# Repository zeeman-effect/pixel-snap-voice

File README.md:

# pixel-snap-voice

A one-off slim rectangular **voice-note recorder** that snaps to the back of a **Google Pixel 10** using Pixelsnap / Qi2 magnets (MagSafe-style accessory rings work). It records raw WAV files, charges and dumps data over USB, can share those files over its own Wi-Fi network, and leaves transcription to a computer.

This repo holds hardware, firmware, simulation, and (later) a local transcription helper. The first board is meant to be ordered from quick-turn services after the sims pass — not invented from unsolved problems.

## What it is

- ESP32-S3-MINI-1U, **ES8311 codec** (I2S master), analog MEMS mic, class-D speaker (or headphone jack if thickness loses)
- 16-bit PCM WAV, **48 kHz** mono (~173 MB/hour)
- USB Mass Storage when plugged into a computer
- Wi-Fi share: the recorder makes its own WPA2 network and serves `/recordings` in a browser (and read-only WebDAV)
- No on-device transcription, no Bluetooth file transfer, no wireless charging through the accessory

MCU choice and why we did **not** switch off Espressif: [`docs/audio-platform.md`](docs/audio-platform.md).

## Repo layout

| Path | Role |
| --- | --- |
| [`docs/architecture.md`](docs/architecture.md) | Electrical + mechanical constraints |
| [`docs/audio-platform.md`](docs/audio-platform.md) | Why ESP32-S3 + codec, not a different MCU |
| [`docs/bom.md`](docs/bom.md) | Living bill of materials |
| [`docs/manufacturing.md`](docs/manufacturing.md) | JLCPCB / print / CNC |
| [`docs/phase0-bringup.md`](docs/phase0-bringup.md) | Off-the-shelf DevKit path before a custom PCB |
| [`firmware/`](firmware/) | ESP-IDF app + portable recorder/WAV core |
| [`sim/host/`](sim/host/) | `HOST_SIM` HAL, tests, PC WAV fixture |
| [`sim/spice/`](sim/spice/) | USB → charger → battery → 3.3 V model |
| [`hardware/cad/`](hardware/cad/) | Parametric envelope (OpenSCAD) + keepout checker |
| [`hardware/kicad/`](hardware/kicad/) | KiCad 10 schematic / PCB / stackup notes |
| [`scripts/`](scripts/) | `check_gates.py` ship gate, `setup-ubuntu.sh` toolchain install |
| [`.claude/skills/`](.claude/skills/) | Agent skills, including vendored [KiStack](https://github.com/American-Embedded/kistack) KiCad workflows |
| [`software/`](software/) | Local whisper.cpp CLI (`transcribe.py`) |

## Set up a machine

The hardware checks need KiCad 10 (`kicad-cli` plus its `pcbnew` Python module), the host sim needs CMake and a C compiler, the power-path sim needs ngspice, and `route_pcb.py` needs the freerouting autorouter.

**Ubuntu 24.04** (a dev box, CI runner, container, or a cloud coding agent): from the repo root, run

```bash
bash scripts/setup-ubuntu.sh
```

It installs build-essential, CMake, ngspice, KiCad 10 from the official KiCad PPA, and freerouting 2.4.1 into `/opt/freerouting`, then builds the host sim into `build/host`. It is safe to run again. It uses `sudo` for apt unless it is already root. For a cloud agent or CI job, make that command the environment's setup or install step.

**Windows or macOS:** there is no script. Install by hand:

- [KiCad 10](https://www.kicad.org/download/). Run the `pcbnew` scripts (`generate_pcb.py`, `route_pcb.py`, `check_placement.py`) with KiCad's bundled `python`, not system Python.
- CMake and a C compiler (MSVC, MinGW, or clang).
- [ngspice](https://ngspice.sourceforge.io/), only for the power-path sim.
- [freerouting](https://github.com/freerouting/freerouting/releases), only for `route_pcb.py`. Put it on `PATH`, unpack it to `~/.local/opt/freerouting/`, or set `PSV_FREEROUTING` to the launcher.

Python packages are in [`requirements.txt`](requirements.txt): `numpy` (for `route_pcb.py`) and `cadquery` (only for the metal tray STEP). Install them into a virtual environment made with `--system-site-packages`, so KiCad's `pcbnew` stays importable. The file also lists what comes with KiCad and Blender instead of pip.

Firmware needs ESP-IDF on top of this. See [`firmware/README.md`](firmware/README.md).

## Simulate first

From the repo root, with CMake and a C compiler (MSVC, MinGW, or clang):

```bash
cmake -S sim/host -B build/host
cmake --build build/host
./build/host/recorder_test      # Windows: build/host/Debug/recorder_test.exe
./build/host/recorder_sim
```

Mechanical keepouts (Python 3, no extra packages):

```bash
python hardware/cad/check_envelope.py
```

Power path (needs [ngspice](https://ngspice.sourceforge.io/)):

```bash
ngspice -b sim/spice/power_path.cir
```

## Physical phases

0. Prove capture **and playback** on an Espressif voice board (Korvo-2 / ESP-BOX) or OpenMic; Sense is recorder-core only. See [`docs/phase0-bringup.md`](docs/phase0-bringup.md).
1. Custom slim PCB + 3D-printed chassis + bought magnet ring (JLCPCB).
2. Same PCB in CNC **6061 aluminum** (not steel).

After you change the product schematic sources, run `python hardware/kicad/recorder/generate_recorder.py` then `python hardware/kicad/recorder/verify_schematic.py`. That overwrites sheets only. It does not write `recorder.kicad_pcb`. Edit the board (or rebuild it on purpose with `generate_pcb.py`) until traces and DRC are clean. Do not order boards until `python scripts/check_gates.py` is clean **and** `kicad-cli pcb drc` is clean **and** `kicad-cli` has written Gerbers from `hardware/kicad/recorder/recorder.kicad_pcb`.

## Transcription

Dump WAVs over USB, then run a local model (whisper.cpp) on the computer:

```bash
python software/transcribe.py /path/to/recordings/20260828-181742.wav
```

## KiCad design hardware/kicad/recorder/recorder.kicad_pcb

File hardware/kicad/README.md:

# KiCad — custom slim PCB

4-layer **0.8 mm**, OSP. Origin = magnet-ring center (same as CAD). USB is full speed and deliberately **not** impedance controlled — see [Stackup](#stackup-jlc-4-layer-08-mm).

Two trees only:

- **Product:** `recorder/` — schematic + PCB. Open `recorder.kicad_pro`.
- **Learning:** `example_project/` — hand-made KiCad 10 sandbox. Not product truth. Leave it alone unless you are in that lesson.

```bash
python hardware/kicad/recorder/generate_recorder.py
python hardware/kicad/recorder/verify_schematic.py
python hardware/kicad/recorder/route_pcb.py --planes-only   # needs pcbnew
python scripts/check_gates.py
```

`route_pcb.py` and `generate_pcb.py` need an interpreter that can `import pcbnew`. On Linux that is the system `python3`; on Windows use `%LOCALAPPDATA%\Programs\KiCad\10.0\bin\python.exe`.

`generate_recorder.py` overwrites the recorder sheets. It does not write `recorder.kicad_pcb`. `route_pcb.py --planes-only` loads that board and pours copper. It does not move parts. Close the recorder project in KiCad before running either script.

`generate_pcb.py` rebuilds the board from scratch and wipes copper. Run it only when you intend a placement reset, then pour and route again. `route_pcb.py` with no flag does the whole job: it clears copper, lays the planes, hand-routes the parts an autorouter cannot do (the USB-C escape, the D+/D− pair, the fine-pitch fanouts), locks them, hands the rest to freerouting over Specctra DSN/SES, then pours, stitches and repairs until `kicad-cli pcb drc` is clean. Footprint XY: [`recorder/placement.json`](recorder/placement.json). Keep it in sync with the board. CAD envelope is `hardware/cad/params.json` + `case.scad`. Those numbers can move when the case or board moves.

`check_gates.py` checks the files that are already on disk. It does not regenerate.

Sheets: `mcu_usb`, `audio`, `power`, `io` (global labels join them). Pin map: [`pinmap.md`](pinmap.md).

Before a fab upload, land patterns must be datasheet footprints, `kicad-cli pcb drc` must be clean, and `kicad-cli` must write `fab/` from `recorder.kicad_pcb`. `check_gates.py` now does the last two itself. J2 (dev / USB-C variant) is `PSV:USB_C_Receptacle_HRO_TYPE-C-31-M-13C`, the LCSC EasyEDA land for C2848620 copied 1:1 with the contact heels trimmed to 0.20 mm off its own board slot, which the footprint carries on Edge.Cuts.

## Design rules

The board is checked against JLCPCB's published standard 4-layer FR-4 capability rather than a set of house numbers, so a green DRC means the fab can build it. Global floors are `DESIGN_RULES` in [`recorder/generate_pcb.py`](recorder/generate_pcb.py); each entry names the JLC figure it comes from and says where it is deliberately tighter. Two checks depend on what kind of item is involved and cannot be a single global minimum, so they live in [`recorder/recorder.kicad_dru`](recorder/recorder.kicad_dru): pad hole-to-hole spacing at 0.6 mm (JLC's floor is 0.45 mm; 0.6 mm keeps the plated-hole tolerance) and minimum non-plated hole (0.5 mm).

What the board actually holds, against what JLC allows:

| | Board | JLC standard |
| --- | --- | --- |
| Track width | 0.15 mm | 0.1016 mm |
| Via | 0.6 mm on a 0.3 mm drill | 0.25 mm on 0.15 mm |
| Pad hole-to-hole | 0.62 mm | 0.45 mm |
| Via hole-to-hole | 0.30 mm | 0.20 mm |
| Hole to copper | 0.30 mm | 0.20 mm |
| Copper to routed edge | 0.30 mm | 0.20 mm |
| Silk text | 1.0 mm on a 0.15 mm stroke | 1.0 mm on 0.15 mm |

Hole-to-copper is held at 0.3 mm rather than JLC's 0.2 mm because non-plated holes carry a ±0.2 mm diameter tolerance: a 1.7 mm mounting hole can come back 0.1 mm larger in radius and eat the difference. The same margin is what forced MK1's ring pad outward, since the stock Infineon land leaves only 0.18 mm to the sound port.

## Stackup (JLC 4-layer 0.8 mm)

| Layer | Role | Copper |
| --- | --- | --- |
| F.Cu | signals, tall parts (battery side) | 1 oz |
| prepreg | ~0.10 mm | |
| In1.Cu | GND plane | 0.5 oz |
| core | ~0.53 mm | |
| In2.Cu | **VDD33** pour | 0.5 oz |
| prepreg | ~0.10 mm | |
| B.Cu | GND, **flat toward the shunt / phone** | 1 oz |

USB pair: 0.20 mm traces on a 0.40 mm pitch, F.Cu over the solid In1 GND plane. **Not impedance controlled, and no controlled-impedance option needs ordering.** The ESP32-S3 USB peripheral is full speed only (12 Mbps, no high-speed PHY), and 90 Ω on this 0.1 mm top prepreg would need roughly 0.06 mm traces, half what a quick-turn fab will run. The geometry above lands near 75 Ω differential by first-order microstrip, which is fine at full-speed edge rates. If a later revision ever needs high-speed USB, thicken the top prepreg first.

The pair is long for USB. That is placement, not sloppiness: U1's USB pads sit on the module's top row, the far side of a 15.9 mm module from J2 on the phone-bottom edge, and the castellations leave 0.05 mm between pads, so the pair has to go around the module rather than under it. The millimetres used to be typed here too. They are measured off the board by `route_pcb.py` and written to [`recorder/placement.json`](recorder/placement.json) under `routing.usb`; read them there, because a copy in prose goes stale the first time anyone reroutes.

## Keepouts

- No tall parts on B.Cu except the taped pouch and the BT1 pads (phone / shunt side)
- Mic on the phone-right long edge
- USB-C (**J2**, dev variant) at (7.0, −38.1) on F.Cu, rot 180, mouth flush with the phone-bottom edge, in a 9.24 × 6.54 mm slot. R2 / R3 (CC Rd) and U7 sit just north of its contact row
- Battery pads (**BT1**) on B.Cu at (−17, 35), land `PSV:Battery_Pigtail_2P`. USB-C J2 is the only 5 V inlet
- **J3** is MK MKDV4GCL-ABB (512 MB) on land `PSV:ZDSD32GLGEAG` at (−22, −18) on F.Cu. Not a card socket. Pins 3 CLK, 4 ground, 5 CMD, 8 power.
- Analog island (U2, U8, MK1, Y1) off **VDD33**
- Analog footprint centres off the magnet circle (`check_placement.py`)
- Nothing taller than ~0.5 mm under the 51.5 × 66 mm pouch tape at (0, 0)
- MINI-1U module (15.4 × 15.4 mm). No PCB-antenna keepout. IPEX takes a lid W.FL / MHF III pigtail
- 4× M1.6 holes. No fiducials on this first pass.

Gerbers: `fab/` after `scripts/check_gates.py`, which runs `kicad-cli pcb drc` first and then writes the Gerbers, both drill files, the pick-and-place CSV, `recorder-jlc.zip` and the JLCPCB CSVs (`jlcpcb_bom.csv`, `jlcpcb_cpl.csv`, `jlcpcb_extra.csv`, via [`recorder/generate_jlc.py`](recorder/generate_jlc.py)) in one pass from `recorder.kicad_pcb`. Do not hand-export or hand-edit only part of that set: a drill file that does not match the copper is a scrap board, and a pick-and-place row that does not match it is a misassembled one. Both CSVs were hand-kept until four decoupling capacitors were found still sitting at their pre-route coordinates. The gate runs DRC at every severity and with `--schematic-parity`, then runs it again with `--refill-zones` and refuses to plot if the answers differ — `kicad-cli` plots the fill stored in the board, so a stale pour would ship while DRC quietly refilled and passed it.

Open `recorder/recorder.kicad_pro` in KiCad 10. ERC/DRC in KiCad is the last human glance. The Python checks are the repo gate.

U1 comes from `hardware/cad/params.json` `mcu`. Change the module there, then update the recorder schematic sources and regenerate the sheets.

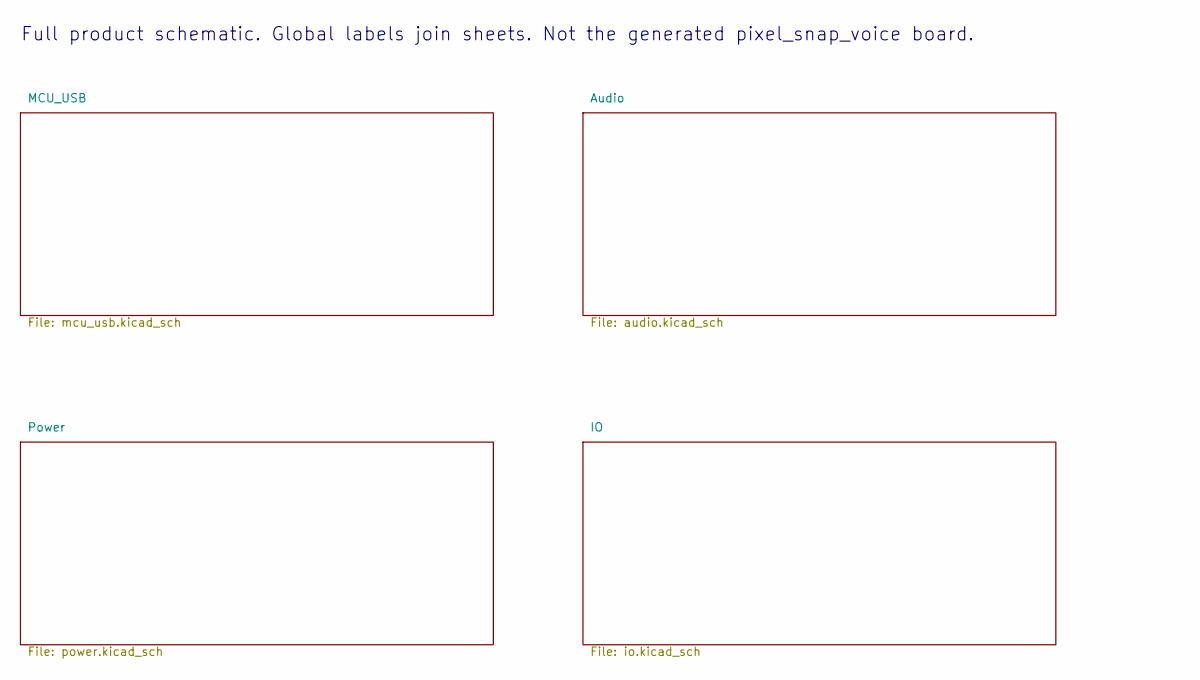
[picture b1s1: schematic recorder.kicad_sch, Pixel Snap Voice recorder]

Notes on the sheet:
Full product schematic. Global labels join sheets. Not the generated pixel_snap_voice board.

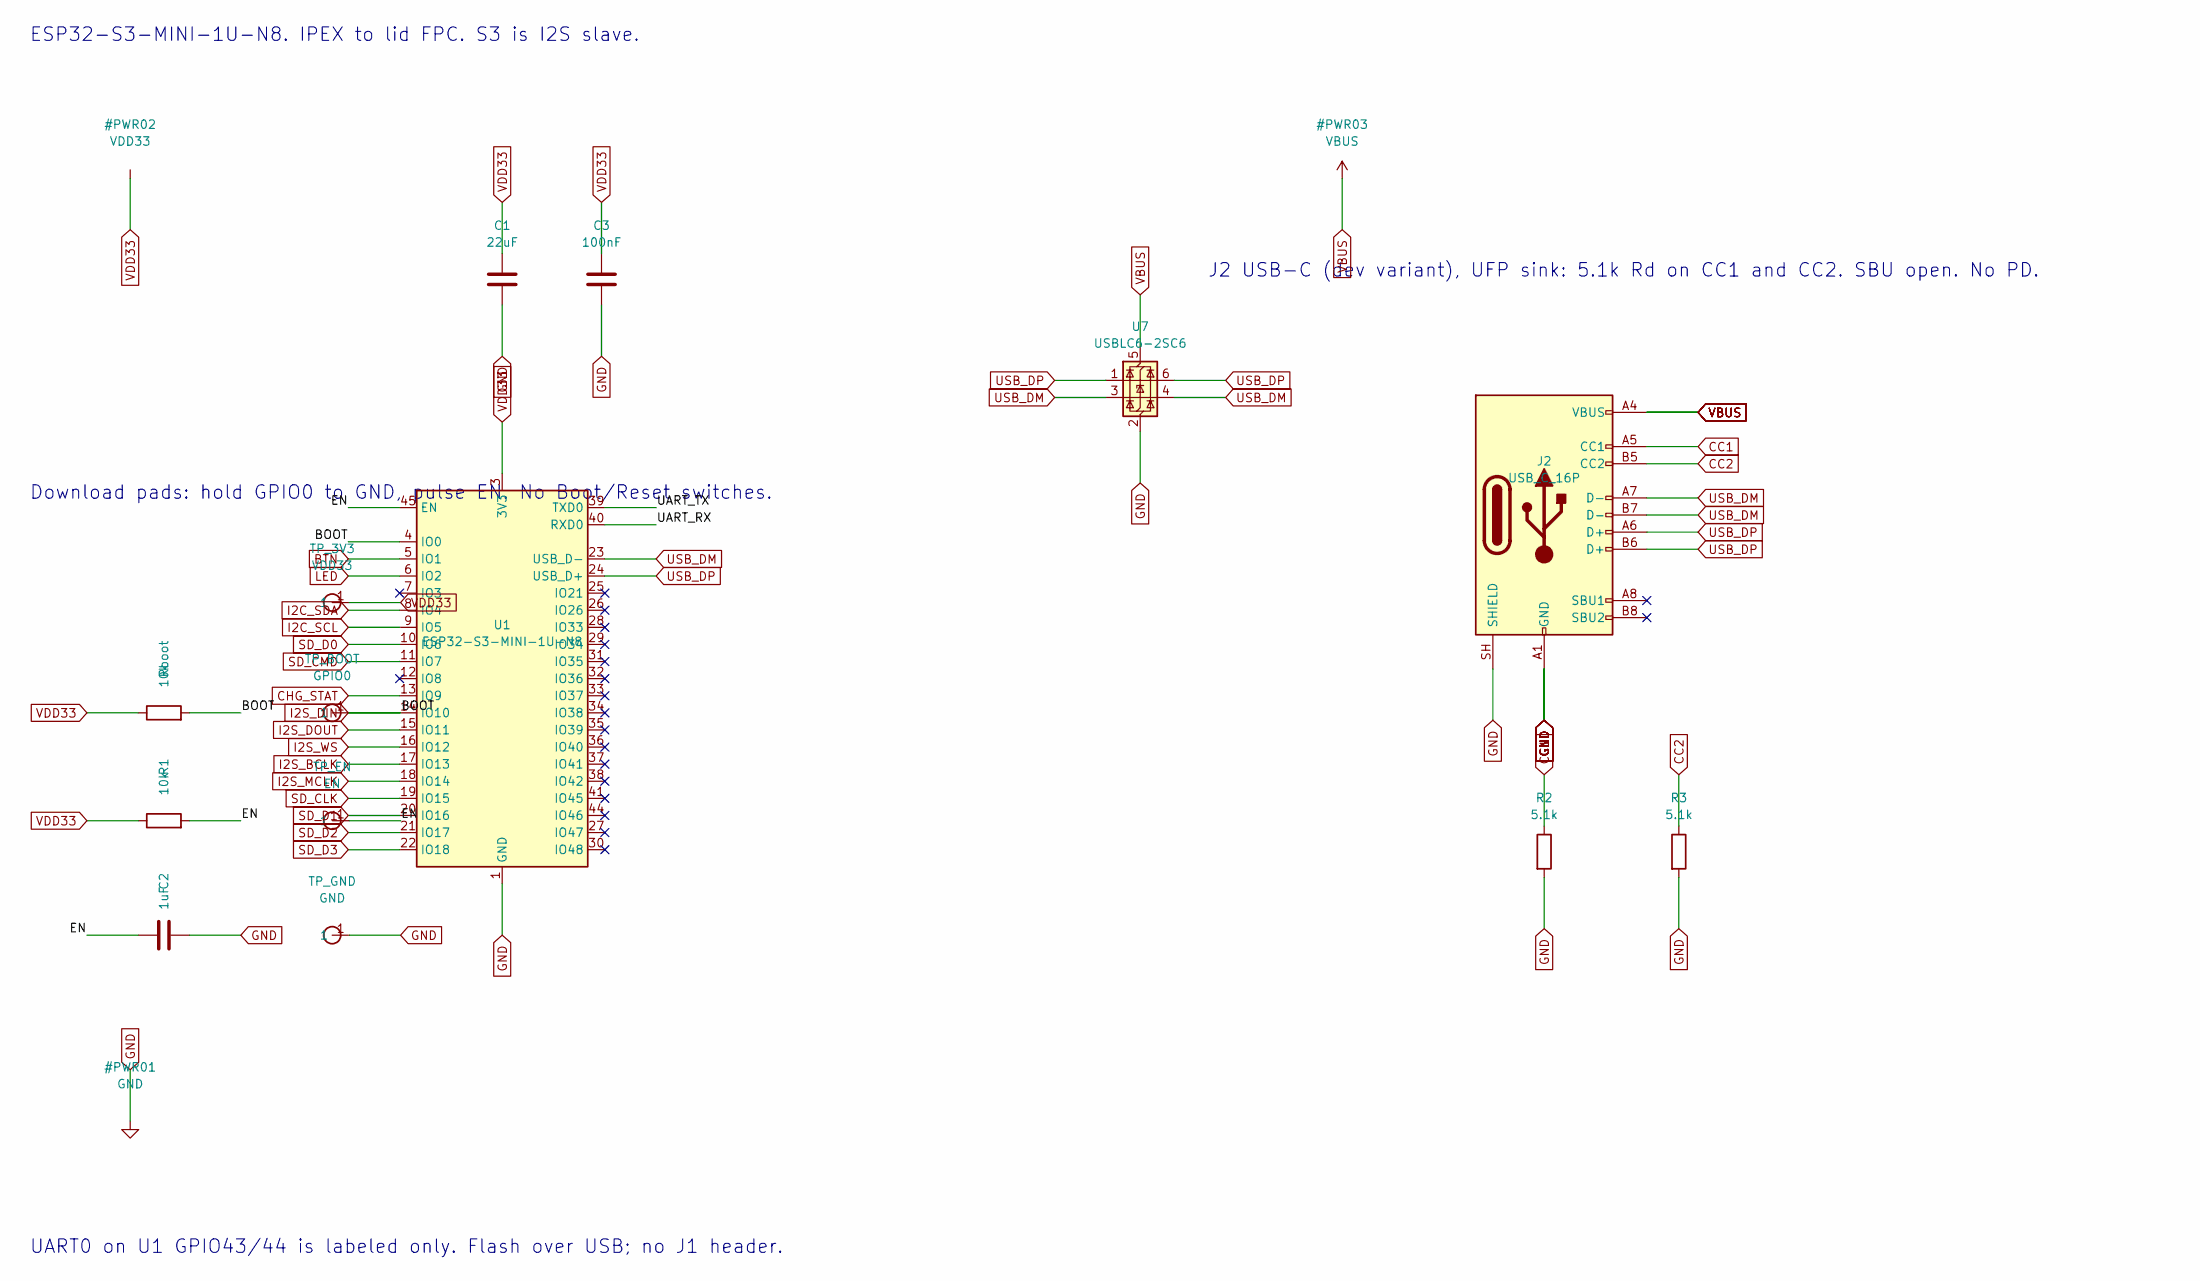
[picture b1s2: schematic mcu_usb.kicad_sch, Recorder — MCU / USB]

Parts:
C1: 22uF; C_0805_2012Metric
C2: 1uF; C_0603_1608Metric
C3: 100nF; C_0603_1608Metric
J2: USB_C_16P; USB_C_Receptacle_HRO_TYPE-C-31-M-13C
R1: 10k; R_0603_1608Metric
R2, R3: 5.1k; R_0603_1608Metric
Rboot: 10k; R_0603_1608Metric
TP_3V3: VDD33; TestPoint_Pad_D1.5mm
TP_BOOT: GPIO0; TestPoint_Pad_D1.5mm
TP_EN: EN; TestPoint_Pad_D1.5mm
TP_GND: GND; TestPoint_Pad_D1.5mm
U1: ESP32-S3-MINI-1U-N8; ESP32-S3-MINI-1U
U7: USBLC6-2SC6; SOT-23-6

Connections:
/MCU_USB/BOOT: Rboot.2, TP_BOOT.1, U1.4 (IO0)
/MCU_USB/EN: C2.1, R1.2, TP_EN.1, U1.45 (EN)
/MCU_USB/UART_RX: U1.40 (RXD0)
/MCU_USB/UART_TX: U1.39 (TXD0)
BTN: U1.5 (IO1); also elsewhere on the board
CC1: J2.A5 (CC1), R2.1
CC2: J2.B5 (CC2), R3.1
CHG_STAT: U1.13 (IO9); also elsewhere on the board
GND: C1.2, C2.2, C3.2, J2.A1 (GND), J2.A12 (GND), J2.B1 (GND), J2.B12 (GND), J2.SH (SHIELD), R2.2, R3.2, TP_GND.1, U1.1 (GND), U1.2 (GND), U1.42 (GND), U1.43 (GND), U1.46 (GND), U1.47 (GND), U1.48 (GND), U1.49 (GND), U1.50 (GND), U1.51 (GND), U1.52 (GND), U1.53 (GND), U1.54 (GND), U1.55 (GND), U1.56 (GND), U1.57 (GND), U1.58 (GND), U1.59 (GND), U1.60 (GND), U1.61 (GND), U1.62 (GND), U1.63 (GND), U1.64 (GND), U1.65 (GND), U7.2 (GND); also elsewhere on the board
I2C_SCL: U1.9 (IO5); also elsewhere on the board
I2C_SDA: U1.8 (IO4); also elsewhere on the board
I2S_BCLK: U1.17 (IO13); also elsewhere on the board
I2S_DIN: U1.14 (IO10); also elsewhere on the board
I2S_DOUT: U1.15 (IO11); also elsewhere on the board
I2S_MCLK: U1.18 (IO14); also elsewhere on the board
I2S_WS: U1.16 (IO12); also elsewhere on the board
LED: U1.6 (IO2); also elsewhere on the board
PA_EN: U1.12 (IO8)
SD_CLK: U1.19 (IO15); also elsewhere on the board
SD_CMD: U1.11 (IO7); also elsewhere on the board
SD_D0: U1.10 (IO6); also elsewhere on the board
SD_D1: U1.20 (IO16); also elsewhere on the board
SD_D2: U1.21 (IO17); also elsewhere on the board
SD_D3: U1.22 (IO18); also elsewhere on the board
USB_DM: J2.A7 (D-), J2.B7 (D-), U1.23 (USB_D-), U7.3 (I/O2), U7.4 (I/O2)
USB_DP: J2.A6 (D+), J2.B6 (D+), U1.24 (USB_D+), U7.1 (I/O1), U7.6 (I/O1)
VBUS: J2.A4 (VBUS), J2.A9 (VBUS), J2.B4 (VBUS), J2.B9 (VBUS), U7.5 (VBUS); also elsewhere on the board
VDD33: C1.1, C3.1, R1.1, Rboot.1, TP_3V3.1, U1.3 (3V3); also elsewhere on the board

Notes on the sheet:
ESP32-S3-MINI-1U-N8. IPEX to lid FPC. S3 is I2S slave.
Download pads: hold GPIO0 to GND, pulse EN. No Boot/Reset switches.
J2 USB-C (dev variant), UFP sink: 5.1k Rd on CC1 and CC2. SBU open. No PD.
UART0 on U1 GPIO43/44 is labeled only. Flash over USB; no J1 header.

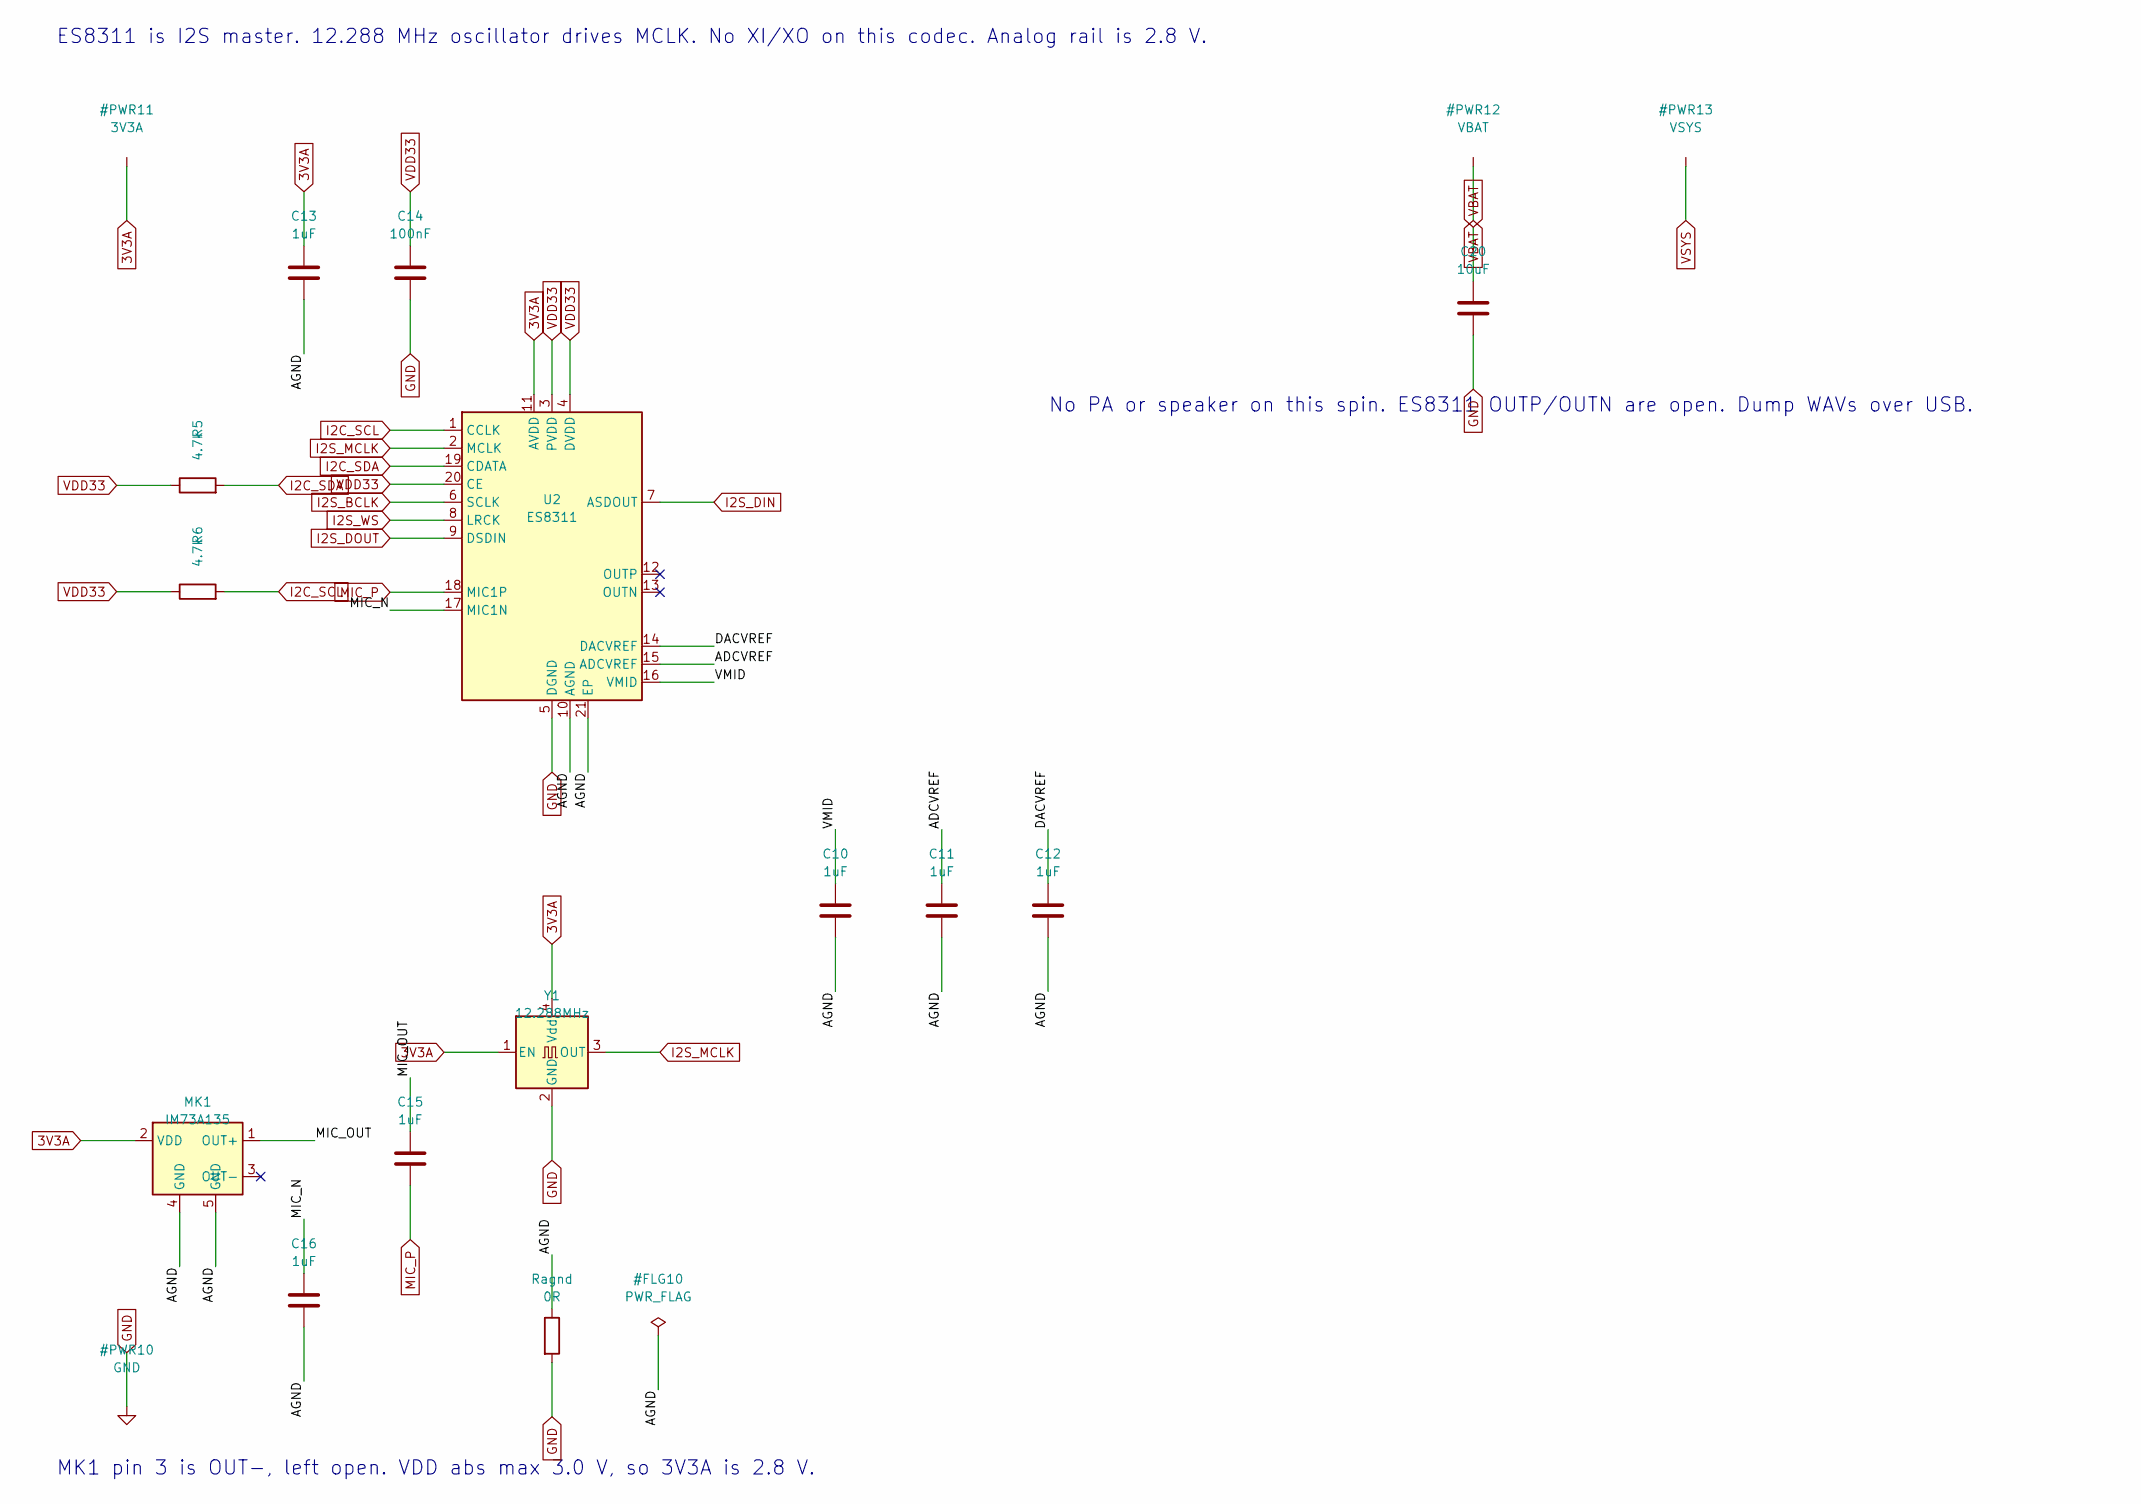
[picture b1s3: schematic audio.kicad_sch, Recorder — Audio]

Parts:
C10, C11, C12, C13, C15, C16: 1uF; C_0603_1608Metric
C14: 100nF; C_0603_1608Metric
C20: 10uF; C_0805_2012Metric
MK1: IM73A135; IM73A135_PG-LLGA-5-3
R5, R6: 4.7k; R_0603_1608Metric
Ragnd: 0R; R_0603_1608Metric
U2: ES8311; QFN-20-1EP_3x3mm_P0.4mm_EP1.65x1.65mm
Y1: 12.288MHz; Oscillator_SMD_Abracon_ASE-4Pin_3.2x2.5mm

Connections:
3V3A: C13.1, MK1.2 (VDD), U2.11 (AVDD), Y1.1 (EN), Y1.4 (Vdd); also elsewhere on the board
/Audio/ADCVREF: C11.1, U2.15 (ADCVREF)
/Audio/AGND: C10.2, C11.2, C12.2, C13.2, C16.2, MK1.4 (GND), MK1.5 (GND), Ragnd.1, U2.10 (AGND), U2.21 (EP)
/Audio/AOUTN: U2.13 (OUTN)
/Audio/AOUTP: U2.12 (OUTP)
/Audio/DACVREF: C12.1, U2.14 (DACVREF)
/Audio/MIC_N: C16.1, U2.17 (MIC1N)
/Audio/MIC_OUT: C15.1, MK1.1 (OUT+)
/Audio/VMID: C10.1, U2.16 (VMID)
GND: C14.2, C20.2, Ragnd.2, U2.5 (DGND), Y1.2 (GND); also elsewhere on the board
I2C_SCL: R6.2, U2.1 (CCLK); also elsewhere on the board
I2C_SDA: R5.2, U2.19 (CDATA); also elsewhere on the board
I2S_BCLK: U2.6 (SCLK); also elsewhere on the board
I2S_DIN: U2.7 (ASDOUT); also elsewhere on the board
I2S_DOUT: U2.9 (DSDIN); also elsewhere on the board
I2S_MCLK: U2.2 (MCLK), Y1.3 (OUT); also elsewhere on the board
I2S_WS: U2.8 (LRCK); also elsewhere on the board
MIC_P: C15.2, U2.18 (MIC1P)
VBAT: C20.1; also elsewhere on the board
VDD33: C14.1, R5.1, R6.1, U2.3 (PVDD), U2.4 (DVDD), U2.20 (CE); also elsewhere on the board

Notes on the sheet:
ES8311 is I2S master. 12.288 MHz oscillator drives MCLK. No XI/XO on this codec. Analog rail is 2.8 V.
MK1 pin 3 is OUT−, left open. VDD abs max 3.0 V, so 3V3A is 2.8 V.
No PA or speaker on this spin. ES8311 OUTP/OUTN are open. Dump WAVs over USB.

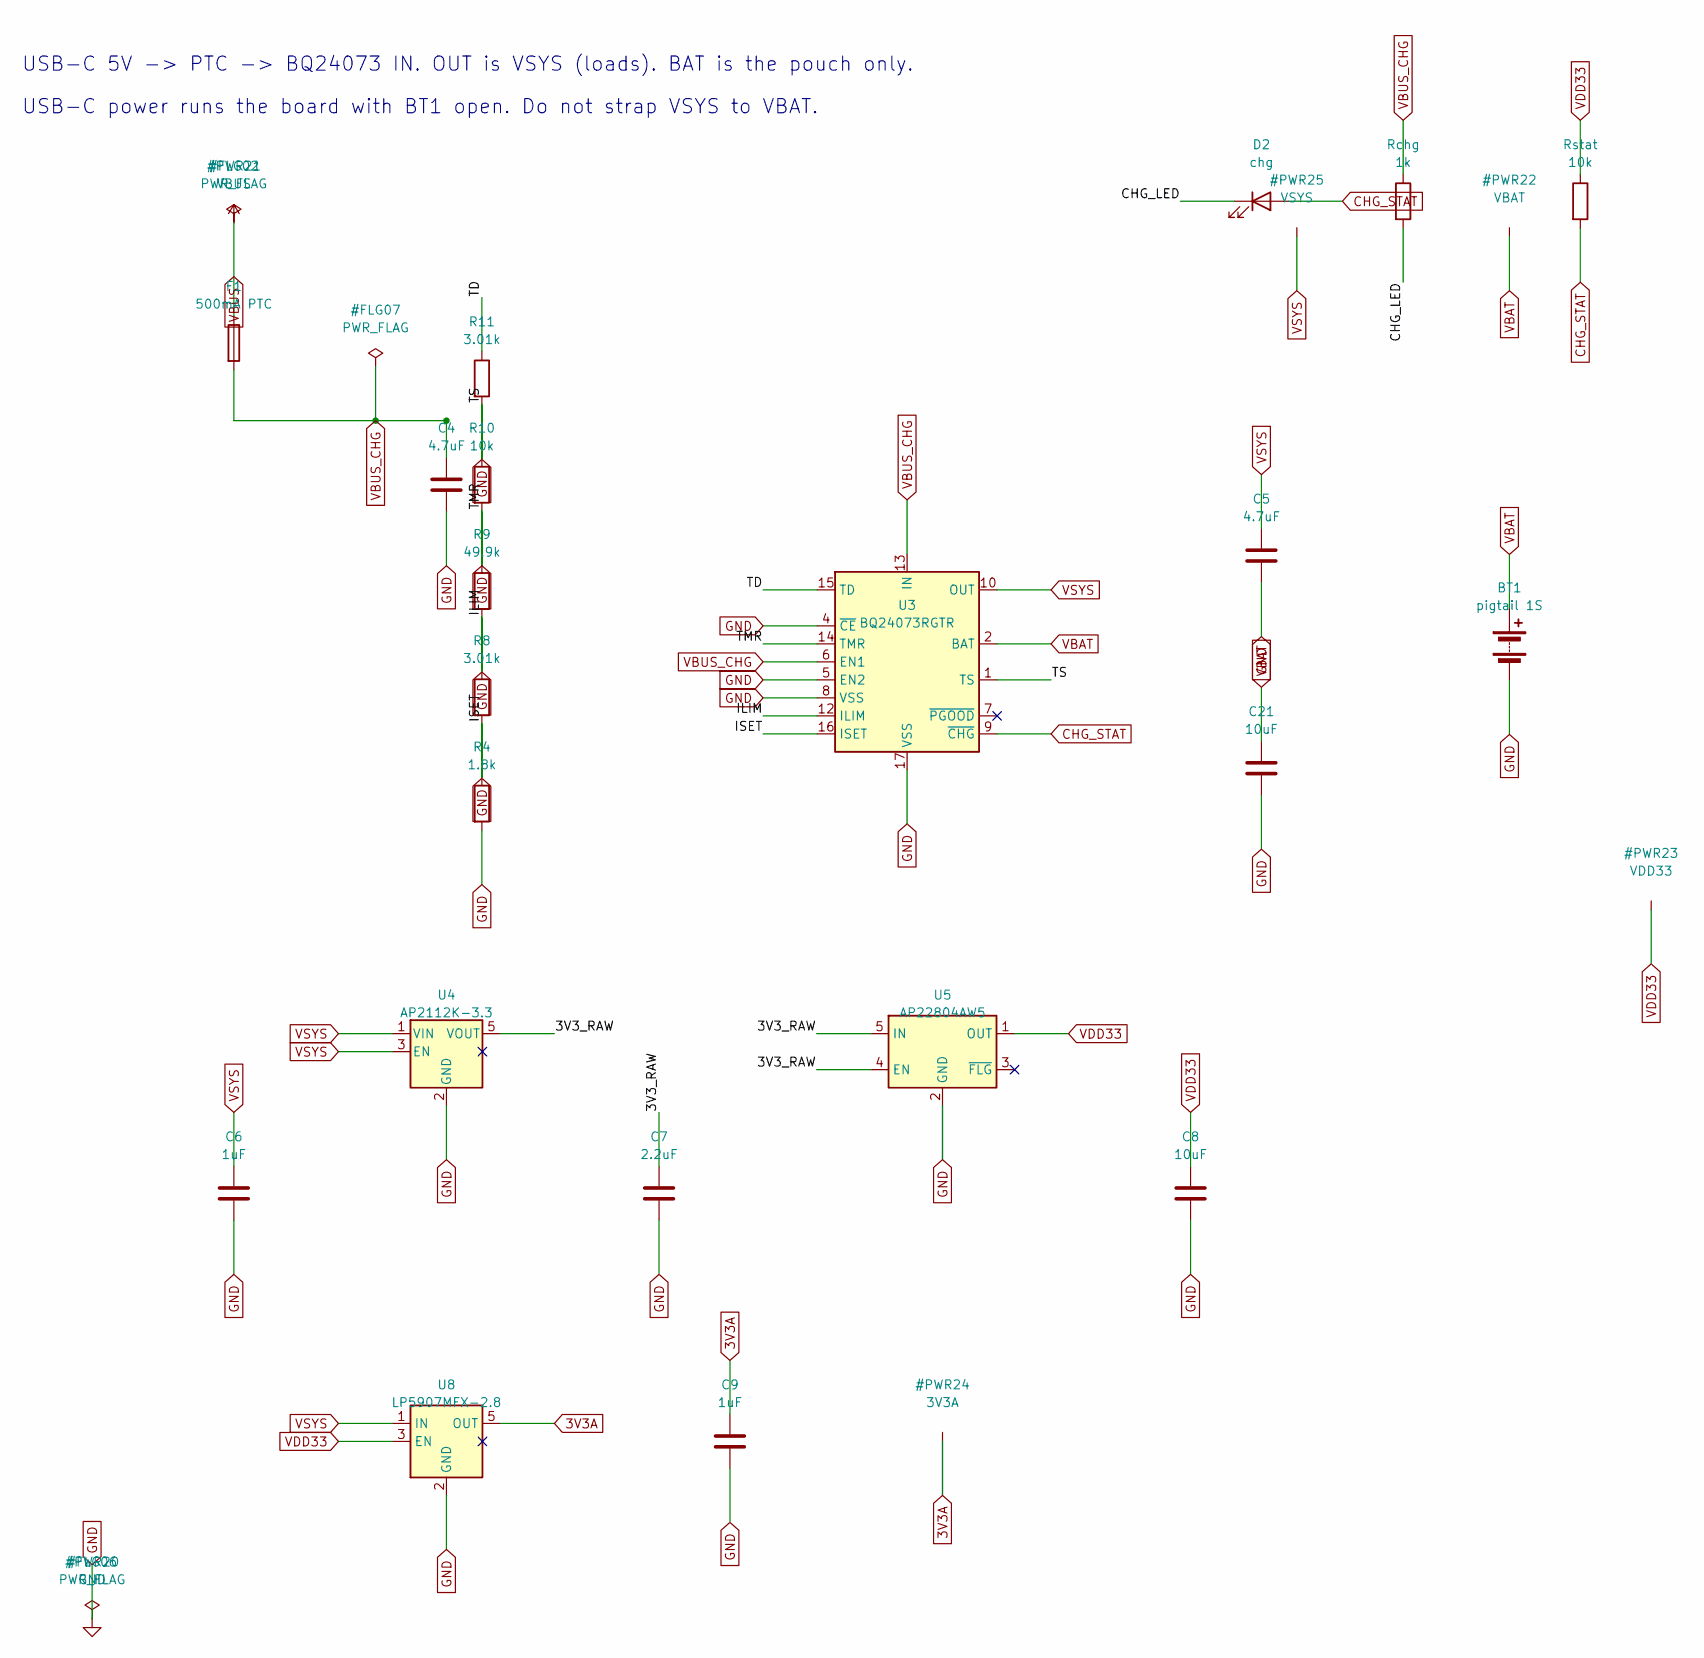
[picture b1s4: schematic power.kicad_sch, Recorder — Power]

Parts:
BT1: pigtail 1S; Battery_Pigtail_2P
C4, C5: 4.7uF; C_0603_1608Metric
C6, C9: 1uF; C_0603_1608Metric
C7: 2.2uF; C_0603_1608Metric
C8: 10uF; C_0805_2012Metric
C21: 10uF; C_0603_1608Metric
D2: chg; LED_0603_1608Metric
F1: 500mA PTC; Fuse_0603_1608Metric
R4: 1.8k; R_0603_1608Metric
R8, R11: 3.01k; R_0603_1608Metric
R9: 49.9k; R_0603_1608Metric
R10: 10k; R_0603_1608Metric
Rchg: 1k; R_0603_1608Metric
Rstat: 10k; R_0603_1608Metric
U3: BQ24073RGTR; VQFN-16-1EP_3x3mm_P0.5mm_EP1.6x1.6mm
U4: AP2112K-3.3; SOT-23-5
U5: AP22804AW5; SOT-23-5
U8: LP5907MFX-2.8; SOT-23-5

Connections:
3V3A: C9.1, U8.5 (OUT); also elsewhere on the board
/Power/3V3_RAW: C7.1, U4.5 (VOUT), U5.4 (EN), U5.5 (IN)
/Power/CHG_LED: D2.1 (K), Rchg.2
/Power/ILIM: R8.1, U3.12 (ILIM)
/Power/ISET: R4.1, U3.16 (ISET)
/Power/TD: R11.1, U3.15 (TD)
/Power/TMR: R9.1, U3.14 (TMR)
/Power/TS: R10.1, U3.1 (TS)
CHG_STAT: D2.2 (A), Rstat.2, U3.9 (~CHG); also elsewhere on the board
GND: BT1.2 (-), C4.2, C5.2, C6.2, C7.2, C8.2, C9.2, C21.2, R4.2, R8.2, R9.2, R10.2, R11.2, U3.4 (~CE), U3.5 (EN2), U3.8 (VSS), U3.17 (VSS), U4.2 (GND), U5.2 (GND), U8.2 (GND); also elsewhere on the board
VBAT: BT1.1 (+), C21.1, U3.2 (BAT), U3.3 (BAT); also elsewhere on the board
VBUS: F1.1; also elsewhere on the board
VBUS_CHG: C4.1, F1.2, Rchg.1, U3.6 (EN1), U3.13 (IN)
VDD33: C8.1, Rstat.1, U5.1 (OUT), U8.3 (EN); also elsewhere on the board
VSYS: C5.1, C6.1, U3.10 (OUT), U3.11 (OUT), U4.1 (VIN), U4.3 (EN), U8.1 (IN)

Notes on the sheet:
USB-C 5V -> PTC -> BQ24073 IN. OUT is VSYS (loads). BAT is the pouch only.
USB-C power runs the board with BT1 open. Do not strap VSYS to VBAT.

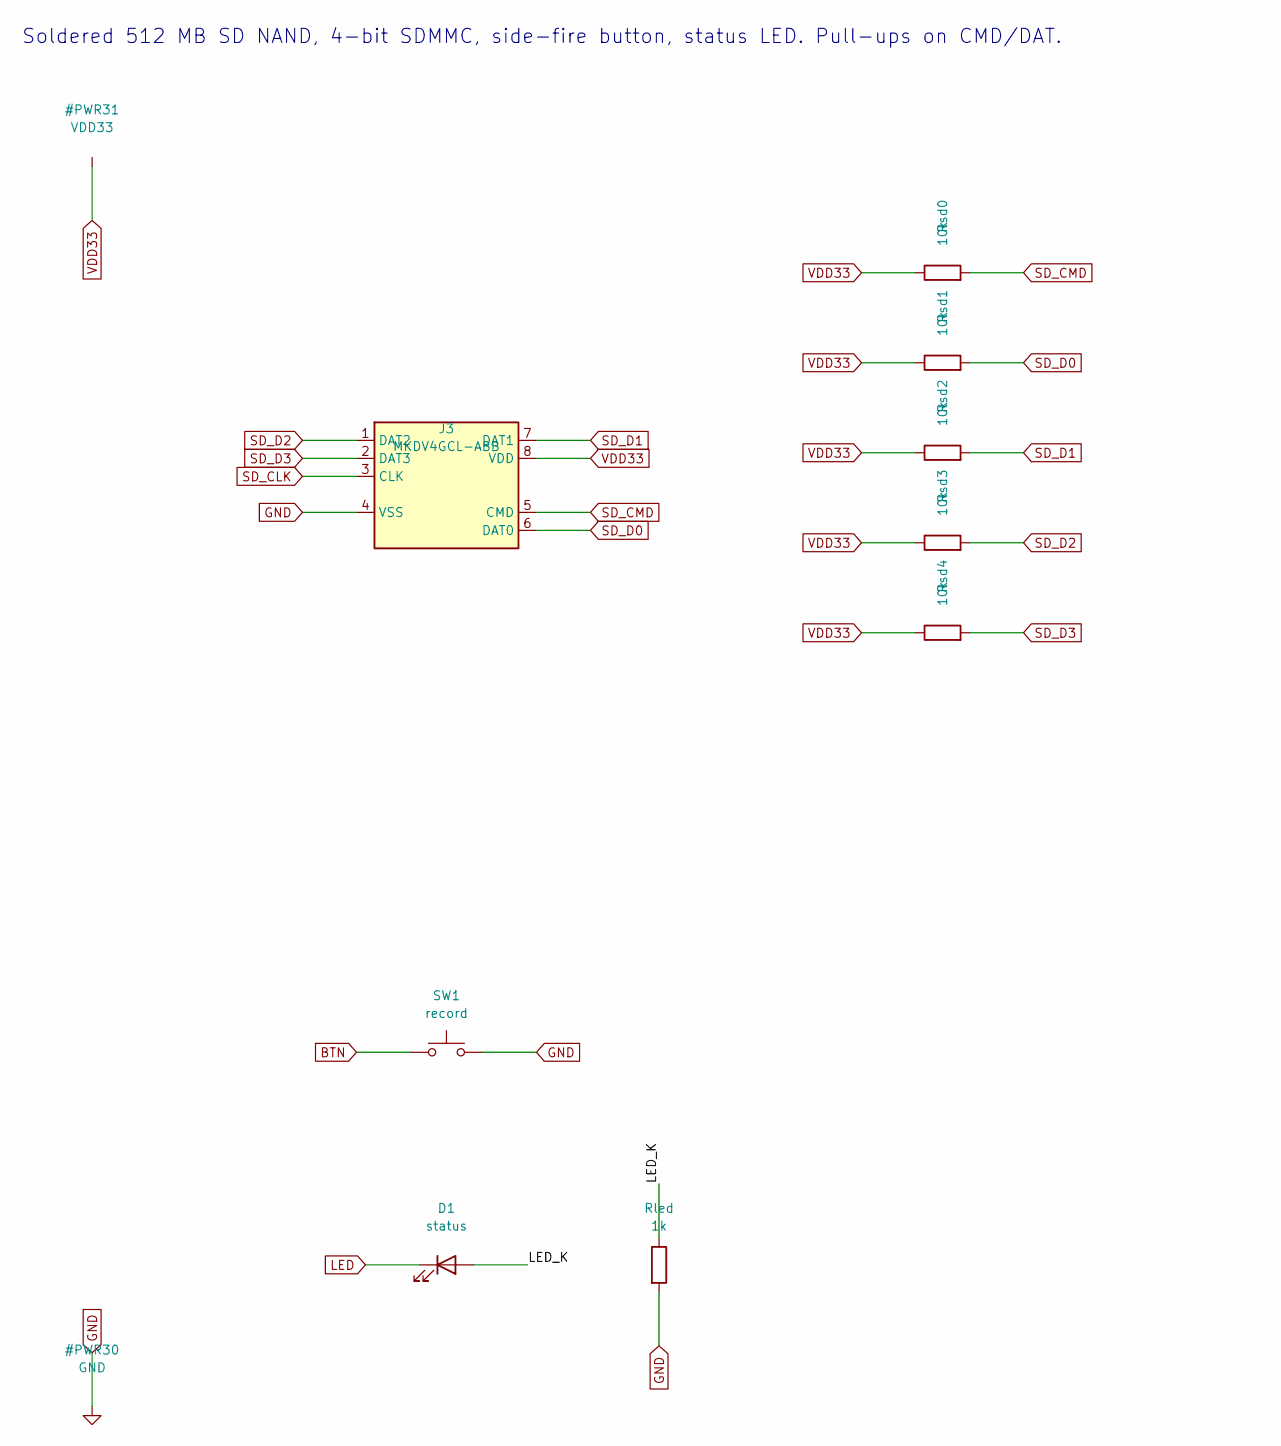
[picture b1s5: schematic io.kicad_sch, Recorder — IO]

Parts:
D1: status; LED_0603_1608Metric
J3: MKDV4GCL-ABB; ZDSD32GLGEAG
Rled: 1k; R_0603_1608Metric
Rsd0, Rsd1, Rsd2, Rsd3, Rsd4: 10k; R_0603_1608Metric
SW1: record; SW_SPST_EVQP7C

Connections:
/IO/LED_K: D1.2 (A), Rled.1
BTN: SW1.1; also elsewhere on the board
GND: J3.4 (VSS), Rled.2, SW1.2; also elsewhere on the board
LED: D1.1 (K); also elsewhere on the board
SD_CLK: J3.3 (CLK); also elsewhere on the board
SD_CMD: J3.5 (CMD), Rsd0.2; also elsewhere on the board
SD_D0: J3.6 (DAT0), Rsd1.2; also elsewhere on the board
SD_D1: J3.7 (DAT1), Rsd2.2; also elsewhere on the board
SD_D2: J3.1 (DAT2), Rsd3.2; also elsewhere on the board
SD_D3: J3.2 (DAT3), Rsd4.2; also elsewhere on the board
VDD33: J3.8 (VDD), Rsd0.1, Rsd1.1, Rsd2.1, Rsd3.1, Rsd4.1; also elsewhere on the board

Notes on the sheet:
Soldered 512 MB SD NAND, 4-bit SDMMC, side-fire button, status LED. Pull-ups on CMD/DAT.

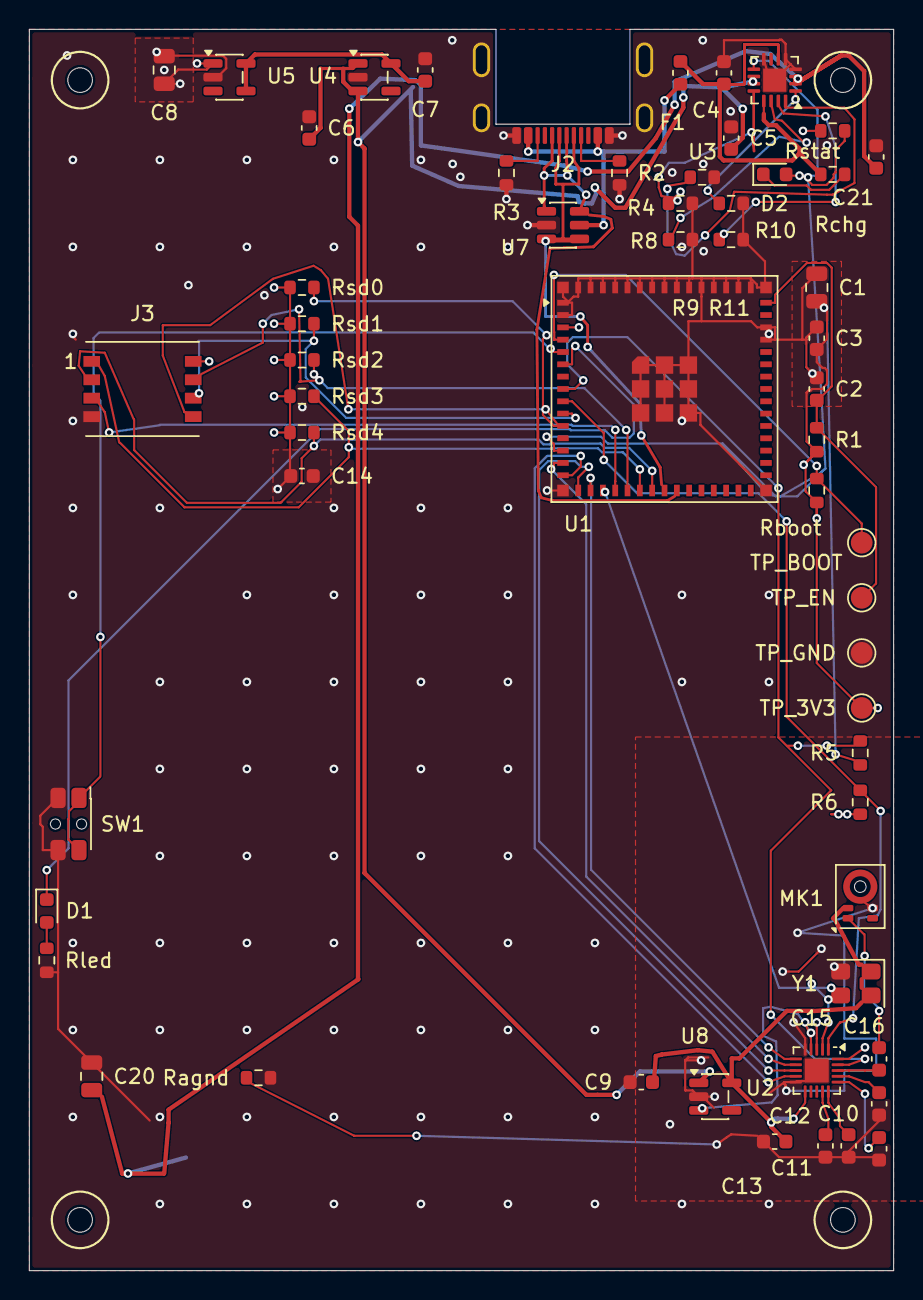
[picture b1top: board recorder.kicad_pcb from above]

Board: 4 copper layers, 59.6 x 85.6 mm, 62 parts (1 on the bottom side), 44 nets.

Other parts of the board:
H1, H2, H3, H4: M1.6 NPTH; MountingHole_1.7mm_M1.6

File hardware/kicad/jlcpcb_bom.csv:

"Comment","Designator","Footprint","LCSC Part #"
"22uF","C1","C_0805_2012Metric","C45783"
"1uF","C2,C6,C9,C10,C11,C12,C13,C15,C16","C_0603_1608Metric","C15849"
"100nF","C3,C14","C_0603_1608Metric","C14663"
"4.7uF","C4,C5","C_0603_1608Metric","C19666"
"2.2uF","C7","C_0603_1608Metric","C23630"
"10uF","C8,C20","C_0805_2012Metric","C15850"
"10uF","C21","C_0603_1608Metric","C96446"
"status","D1","LED_0603_1608Metric","C2286"
"chg","D2","LED_0603_1608Metric","C2286"
"500mA PTC","F1","Fuse_0603_1608Metric","C883095"
"USB_C_16P","J2","USB_C_Receptacle_HRO_TYPE-C-31-M-13C","C2848620"
"MKDV4GCL-ABB","J3","ZDSD32GLGEAG","C7500178"
"IM73A135","MK1","IM73A135_PG-LLGA-5-3","C3171831"
"10k","R1,R10,Rboot,Rsd0,Rsd1,Rsd2,Rsd3,Rsd4,Rstat","R_0603_1608Metric","C25804"
"5.1k","R2,R3","R_0603_1608Metric","C23186"
"1.8k","R4","R_0603_1608Metric","C4177"
"4.7k","R5,R6","R_0603_1608Metric","C23162"
"3.01k","R8,R11","R_0603_1608Metric","C22991"
"49.9k","R9","R_0603_1608Metric","C23184"
"0R","Ragnd","R_0603_1608Metric","C21189"
"1k","Rchg,Rled","R_0603_1608Metric","C21190"
"record","SW1","SW_SPST_EVQP7C","C388883"
"ESP32-S3-MINI-1U-N8","U1","ESP32-S3-MINI-1U","C2980299"
"ES8311","U2","QFN-20-1EP_3x3mm_P0.4mm_EP1.65x1.65mm","C962342"
"BQ24073RGTR","U3","VQFN-16-1EP_3x3mm_P0.5mm_EP1.6x1.6mm","C15220"
"AP2112K-3.3","U4","SOT-23-5","C51118"
"AP22804AW5","U5","SOT-23-5","C3001659"
"USBLC6-2SC6","U7","SOT-23-6","C7519"
"LP5907MFX-2.8","U8","SOT-23-5","C186700"
"12.288MHz","Y1","Oscillator_SMD_Abracon_ASE-4Pin_3.2x2.5mm","C5203546"

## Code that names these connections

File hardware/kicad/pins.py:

#!/usr/bin/env python3
"""Firmware pin map: module GPIO name, net, electrical type. Change this file, custom.h, and pinmap.md together."""

from __future__ import annotations

# GPIO <-> net on U1 (ESP32-S3-MINI-1U-N8). Keep in lockstep with
# firmware/boards/custom.h PSV_*_GPIO macros via check_pins.py.
MCU_PINS = [
    ("3V3", "3V3", "power_in"),
    ("GND", "GND", "power_in"),
    ("EN", "EN", "input"),
    ("GPIO0", "BOOT", "bidirectional"),
    ("GPIO1", "BTN", "bidirectional"),
    ("GPIO2", "LED", "bidirectional"),
    ("GPIO4", "I2C_SDA", "bidirectional"),
    ("GPIO5", "I2C_SCL", "bidirectional"),
    ("GPIO6", "SD_D0", "bidirectional"),
    ("GPIO7", "SD_CMD", "bidirectional"),
    ("GPIO9", "CHG_STAT", "input"),
    ("GPIO10", "I2S_DIN", "input"),
    ("GPIO11", "I2S_DOUT", "output"),
    ("GPIO12", "I2S_WS", "input"),
    ("GPIO13", "I2S_BCLK", "input"),
    ("GPIO14", "I2S_MCLK", "input"),
    ("GPIO15", "SD_CLK", "output"),
    ("GPIO16", "SD_D1", "bidirectional"),
    ("GPIO17", "SD_D2", "bidirectional"),
    ("GPIO18", "SD_D3", "bidirectional"),
    ("GPIO19", "USB_DM", "bidirectional"),
    ("GPIO20", "USB_DP", "bidirectional"),
]
